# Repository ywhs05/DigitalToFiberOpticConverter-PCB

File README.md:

# DigitalToFiberOpticConverter-PCB

### Descripción
Proyecto del laboratorio LabCES de la Universidad de Costa Rica.

<!-- Este circuito tiene como objetivo recibir las señales digitales enviadas por medio de un microcontrolador para luego convertirlas en fibra óptica para que pueda ser leída por los puentes H [PEH2015 de Imperix](DaFO-PCB/Datasheets/PEH2015-PuenteH.pdf) en su entrada de fibra óptica. -->

Este circuito tiene como objetivo recibir una señal PWM digital enviada por medio de un microcontrolador, para luego ser convertida en una señal de fibra óptica para poder ser leída por los puentes H [PEH2015 de Imperix](DaFO-PCB/Datasheets/PEH2015-PuenteH.pdf) en su entrada de fibra óptica.

<!---->

Ahora bien, la placa cuenta con la posiblidad de agregar o no, tiempo muerto a la señal PWM por seguridad de los transistores del puente H. Dicho tiempo muerto es ajustable mediante un trimmer. Por otra parte, es posible negar la señal PWM o no.

En adición, se puede adicionar una placa igual por encima de otra para aprovechar la señal PWM recibida del microcontrolador y se cuentan 3 huecos para colocar los pilares de nylon para su soporte.

Finalmente, se muestran las vistas superior e inferior de la PCB.

### Soporte
- y.huang@ucr.ac.cr
- mauricio.espinoza_bola@ucr.ac.cr

### Estado del proyecto

Se encuentra en proceso de pruebas experimentales.

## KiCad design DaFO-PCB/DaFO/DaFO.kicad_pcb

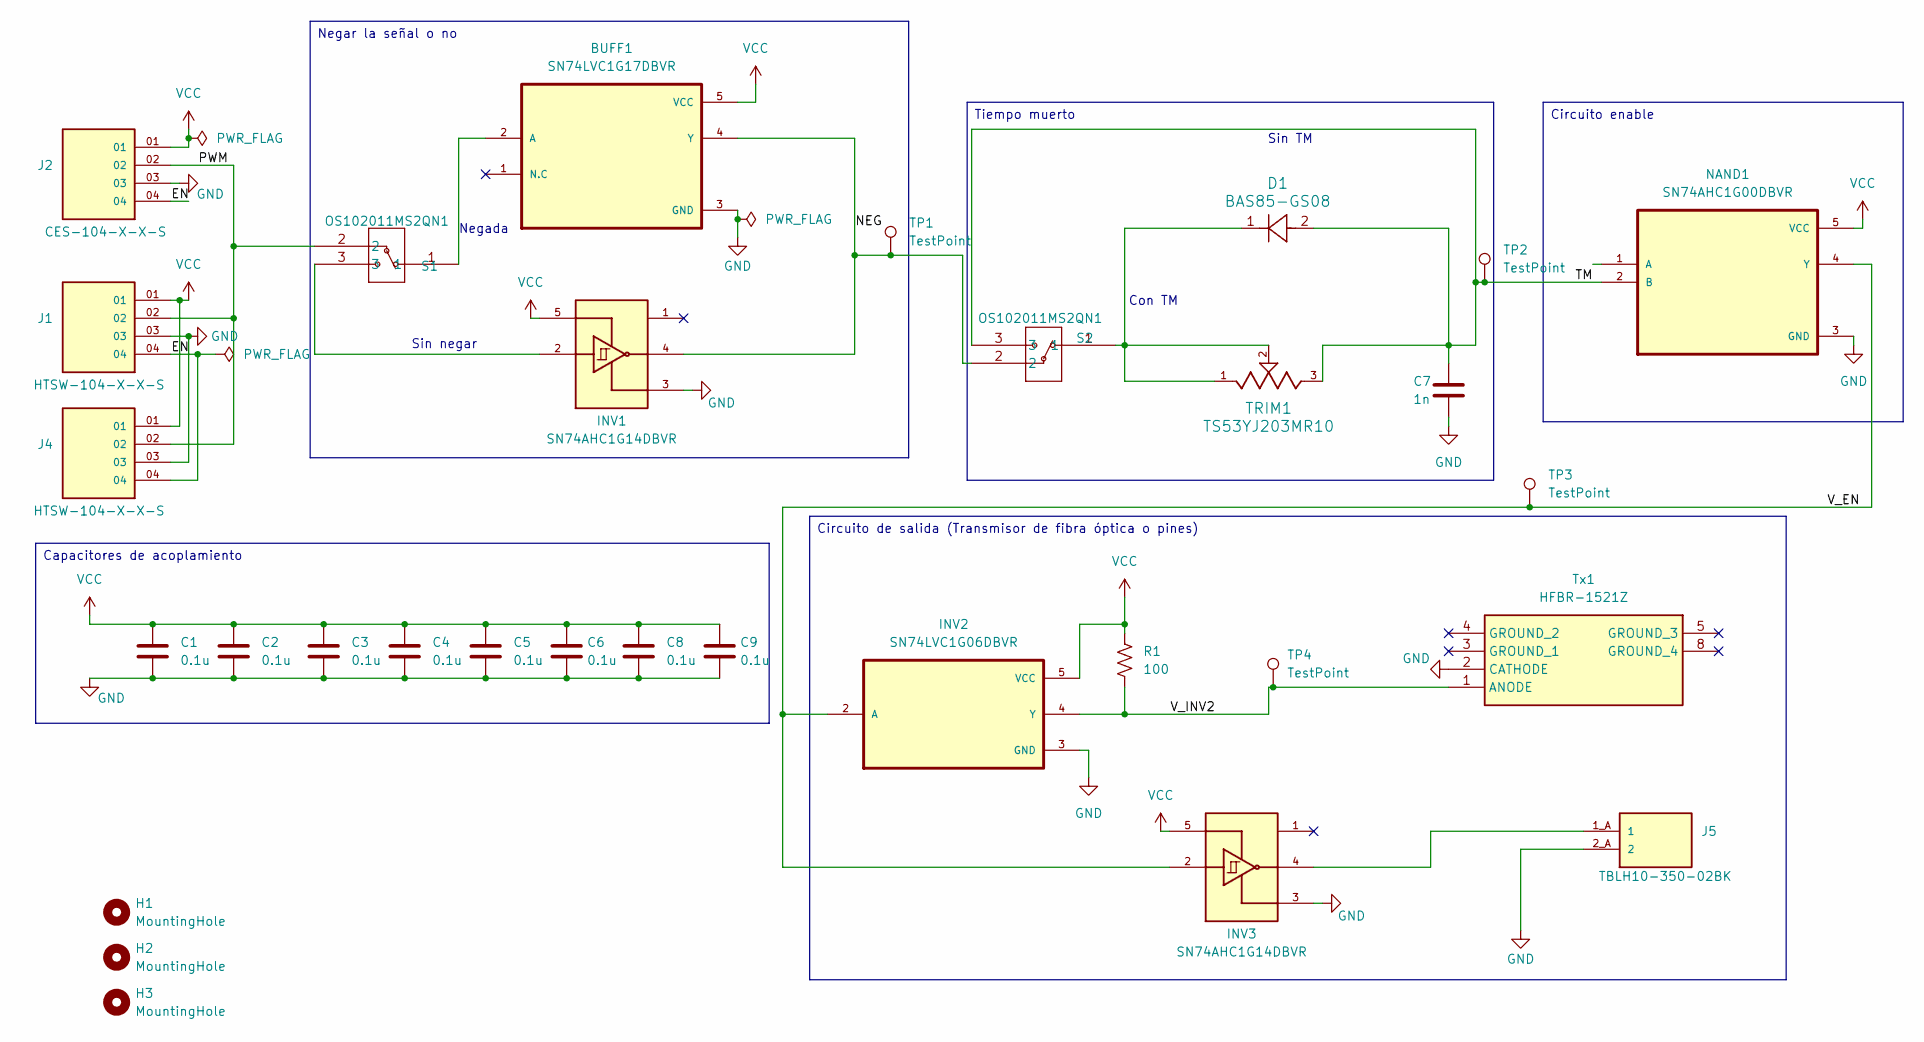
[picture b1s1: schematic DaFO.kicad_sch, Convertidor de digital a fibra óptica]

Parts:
BUFF1: SN74LVC1G17DBVR; SOT95P280X145-5N
C1, C2, C3, C4, C5, C6, C8, C9: 0.1u; C_0603_1608Metric_Pad1.08x0.95mm_HandSolder
C7: 1n; C_0805_2012Metric_Pad1.18x1.45mm_HandSolder
D1: BAS85-GS08; MELF_BAS_8X_VIS
H1, H2, H3: MountingHole; MountingHole_3.2mm_M3
INV1, INV3: SN74AHC1G14DBVR; PARTREV Q
INV2: SN74LVC1G06DBVR
J1, J4: HTSW-104-X-X-S; SAMTEC_HTSW-104-X-X-S; PARTREV B
J2: CES-104-X-X-S; SAMTEC_CES-104-X-X-S; PARTREV A
J5: TBLH10-350-02BK; CUI_TBLH10-350-02BK
NAND1: SN74AHC1G00DBVR; SOT95P280X145-5N
R1: 100; R_0805_2012Metric_Pad1.20x1.40mm_HandSolder
S1, S2: OS102011MS2QN1; OS102011MA1QN1_CNK
TP1, TP2, TP3, TP4: TestPoint; TestPoint_Loop_D1.80mm_Drill1.0mm_Beaded
TRIM1: TS53YJ203MR10; TRIM_3214J-1-203E; PARTREV 06/24
Tx1: HFBR-1521Z; HFBR1521Z; Mouser Part Number 630-HFBR-1521Z

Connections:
/EN: J1.04, J2.04, J4.04
/NEG: BUFF1.4 (Y), INV1.4, S2.2, TP1.1
/PWM: J1.02, J2.02, J4.02, S1.2
/TM: C7.1, D1.2, NAND1.2 (B), S2.3, TP2.1, TRIM1.3
/V_EN: INV2.2 (A), INV3.2, NAND1.4 (Y), TP3.1
/V_INV2: INV2.4 (Y), R1.2, TP4.1, Tx1.1 (ANODE)
GND: BUFF1.3 (GND), C1.2, C2.2, C3.2, C4.2, C5.2, C6.2, C7.2, C8.2, C9.2, INV1.3, INV2.3 (GND), INV3.3, J1.03, J2.03, J4.03, J5.2_A (2), NAND1.3 (GND), Tx1.2 (CATHODE)
unnamed: BUFF1.2 (A), S1.1
unnamed: D1.1, S2.1, TRIM1.1, TRIM1.2
unnamed: INV1.2, S1.3
unnamed: INV3.4, J5.1_A (1)
VCC: BUFF1.5 (VCC), C1.1, C2.1, C3.1, C4.1, C5.1, C6.1, C8.1, C9.1, INV1.5, INV2.5 (VCC), INV3.5, J1.01, J2.01, J4.01, NAND1.5 (VCC), R1.1

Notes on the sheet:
Sin TM
Con TM
Sin negar
Negada
Negar la señal o no
Circuito de salida (Transmisor de fibra óptica o pines)
Tiempo muerto
Capacitores de acoplamiento
Circuito enable

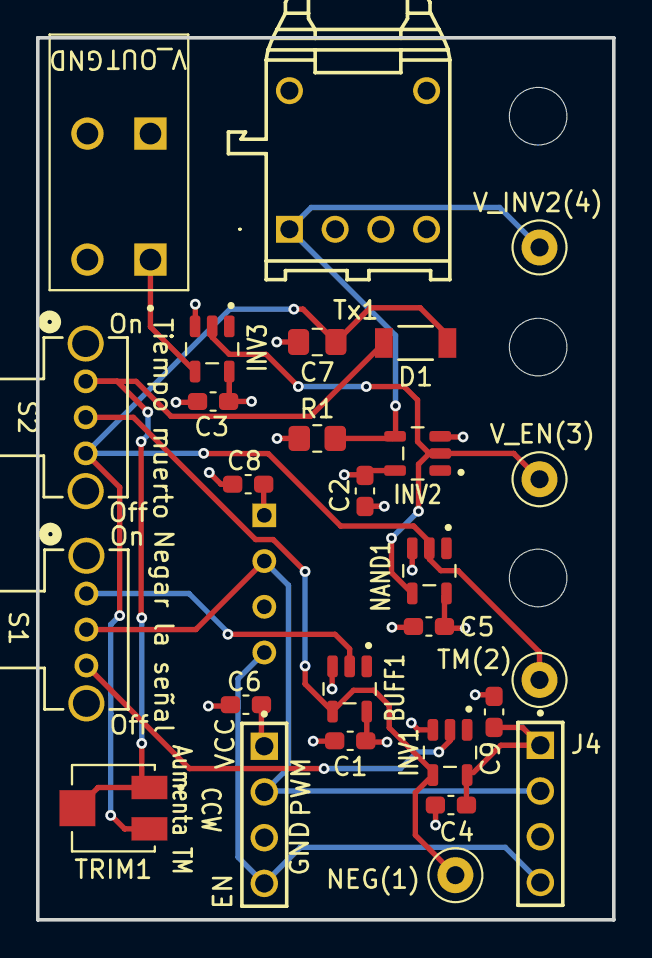
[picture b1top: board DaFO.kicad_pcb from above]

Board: 4 copper layers, 32.0 x 49.0 mm, 31 parts (1 on the bottom side), 12 nets.

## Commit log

2026-01-11 Añadir .gitignore y licencia del proyecto
2026-01-11 Creación del archivo en KiCad
2026-01-11 Añadir archivo README y hojas de datos de interés de componentes a utilizar en la pcb.
2026-01-11 Actualización del README
2026-02-09 Elaboración y diseño del circuito convertidor de digital a fibra óptica modular.
2026-02-09 Actualización del README e información en el esquemático de la placa.
2026-02-10 Corrección del archivo README.
2026-06-14 Cambios para reducir tamaño y a componentes laterales. Creación de archivos de fabricación.
    Se realizaron cambios a la PCB para reducir su tamaño, se cambiaron ciertos componentes y se tienen los archivos de fabricación de la placa.
2026-06-28 Actualización de archivo README.md
    Adición de imágenes y cambio de estado del proyecto.
